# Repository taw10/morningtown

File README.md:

MorningTown: A silent alarm clock
=================================

Description
-----------

MorningTown is a silent alarm clock system based on a Raspberry Pi Pico.

At 7:15am, it lights a single green LED.  At 8am, it additionally lights a red
LED.  Around midday, it turns them both off.  Apart from an over-engineered
configuration system, it does literally nothing else.

Why???
------

You are supposed to get out of bed if you wake up and see the green light, or
perhaps doze until you see the red light as well.  If no lights are on, go
back to sleep.

Huh??
-----

[Awareness of the exact time is bad for your sleep](https://www.techradar.com/health-fitness/mattresses/clock-watching-could-be-killing-your-sleep-why-clocks-have-no-place-in-the-bedroom).

If you're having trouble getting to sleep, seeing the time will add stress
and make it even harder to sleep.  Similarly, knowing that your alarm will go off
shortly can prevent you from relaxing in the morning, and grabbing a valuable
few minutes' extra sleep.

MorningTown reduces information about the time down to a simple signal to say
either "Go back to sleep" or "Get up if you're ready".

In contrast to a clock radio or "artificial sunrise" lamp, there is no danger
of disturbing any other beings who share the room and may run on different
schedules.

I still have a number of questions
----------------------------------

Obviously, you should set an audible alarm clock for important wake-up calls.

Hardware
--------

The Pi Pico's real-time clock loses time when power is removed, so MorningTown
needs either a separate battery-backed RTC module, or to synchronise itself
using NTP on each startup.

### PCB with real-time clock and battery backup

Send the circuit board design in the `pcb` folder
([KiCad](https://www.kicad.org/) format) to your manufacturer of choice.
I have been using [Aisler](https://aisler.net/).

### Cheap and cheerful option

Solder red and green LEDs to GPIOs 22 and 21 respectively of a Raspberry Pi
Pico W, each with a 1.5 kOhm series resistor (you won't need much brightness).
There is a ground pad conveniently placed between these two pins.

You can use other GPIOs if you prefer - see below for configuration
instructions.

Firmware
--------

Edit `compile` to set the path to the [Pico SDK](https://github.com/raspberrypi/pico-sdk),
as well as your WLAN name and password if you are using a Pico W.

The changeover days for daylight savings are hard-coded for Europe (the last
Sundays of March and October).  Unfortunately, a full local time library is far
too big to fit on the Pico, so you will have to figure out the logic yourself
for other time zones.

Run `compile`, then copy `build/morningtown.uf2` to the Pico.

Operation
---------

Connect the Pico to any USB power supply.

When the (optional) test button is held, the LEDs indicate as follows:
* Red: NTP synchronised if applicable, otherwise always on.
* Green: RTC time OK (regardless of source).
* Board LED: WLAN connected if applicable, otherwise always on.

Licence
-------

MorningTown is based on a heavily modified version of one of the Pico SDK
examples (picow-ntp-client), copyright (c) 2022 Raspberry Pi (Trading) Ltd.,
under the BSD 3-clause licence.

MorningTown is free software: you can redistribute it and/or modify it under the
terms of the GNU General Public License as published by the Free Software
Foundation, either version 3 of the License, or (at your option) any later
version.

MorningTown is distributed in the hope that it will be useful, but WITHOUT ANY
WARRANTY; without even the implied warranty of MERCHANTABILITY or FITNESS FOR A
PARTICULAR PURPOSE.  See the GNU General Public License for more details.

You should have received a copy of the GNU General Public License along with
MorningTown.  If not, see <http://www.gnu.org/licenses/>.

About the name
--------------

It's like a railway signal for your sleep:

> Somewhere there is sunshine  
> Somewhere there is day  
> Somewhere there is Morning town  
> Many miles away

- [Malvina Reynolds](https://en.wikipedia.org/wiki/Morningtown_Ride)

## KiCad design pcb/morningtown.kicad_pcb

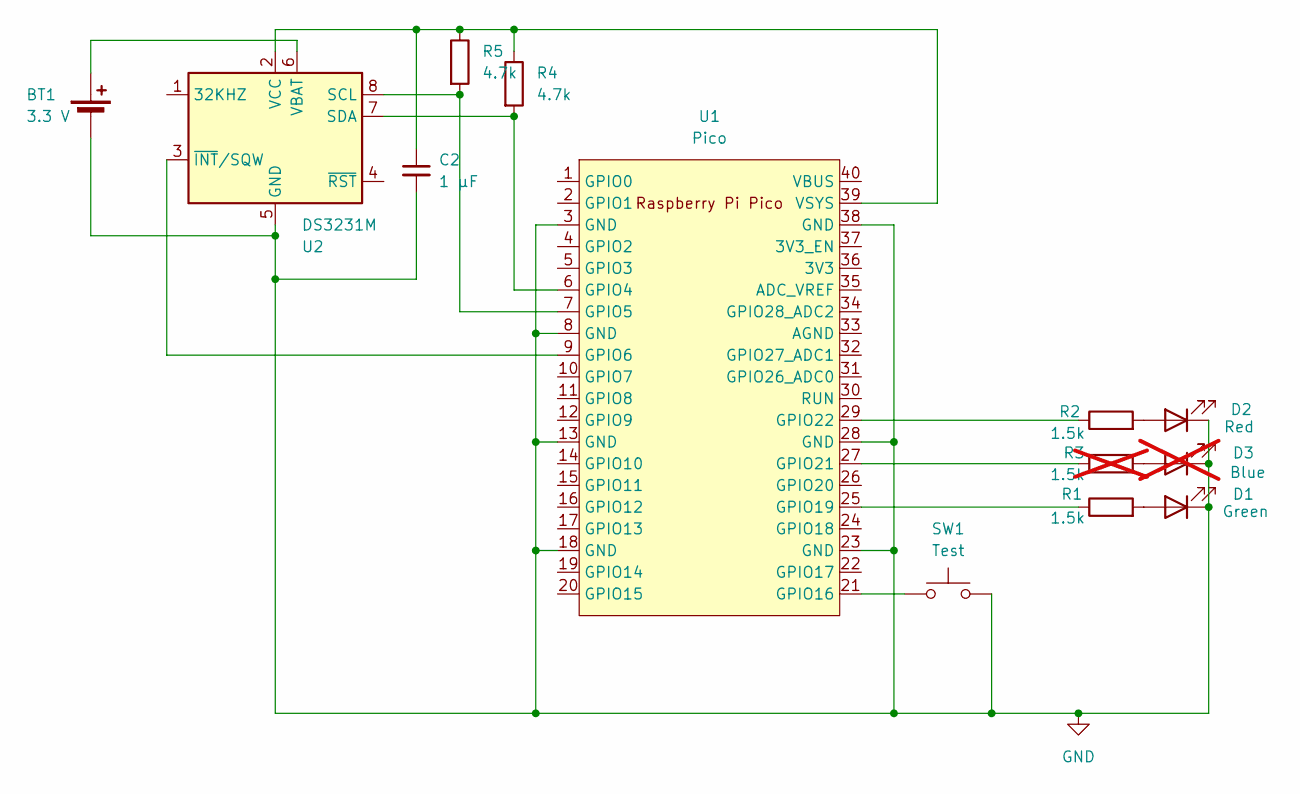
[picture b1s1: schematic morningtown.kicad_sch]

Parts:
BT1: 3.3 V; BatteryHolder_Keystone_3001_1x12mm
C2: 1 µF; C_0805_2012Metric_Pad1.18x1.45mm_HandSolder
D1: Green; LED_D5.0mm
D2: Red; LED_D5.0mm
D3: Blue; LED_D3.0mm; not fitted
R1, R2: 1.5k; R_0805_2012Metric_Pad1.20x1.40mm_HandSolder
R3: 1.5k; R_0805_2012Metric_Pad1.20x1.40mm_HandSolder; not fitted
R4, R5: 4.7k; R_0805_2012Metric_Pad1.20x1.40mm_HandSolder
SW1: Test; SW_PUSH_6mm
U1: Pico; RPi_Pico_W
U2: DS3231M; SOIC-8_3.9x4.9mm_P1.27mm

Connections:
GND: BT1.2 (-), C2.2, D1.1 (K), D2.1 (K), D3.1 (K), SW1.2, U1.3 (GND), U1.8 (GND), U1.13 (GND), U1.18 (GND), U1.23 (GND), U1.28 (GND), U1.38 (GND), U2.5 (GND)
unnamed: BT1.1 (+), U2.6 (VBAT)
unnamed: D1.2 (A), R1.2
unnamed: D2.2 (A), R2.2
unnamed: D3.2 (A), R3.2
unnamed: R4.2, U1.6 (GPIO4), U2.7 (SDA)
unnamed: R5.2, U1.7 (GPIO5), U2.8 (SCL)
unnamed: U1.9 (GPIO6), U2.3 (~INT/SQW)
unnamed: SW1.1, U1.21 (GPIO16)
unnamed: R1.1, U1.25 (GPIO19)
unnamed: R3.1, U1.27 (GPIO21)
unnamed: R2.1, U1.29 (GPIO22)
unnamed: C2.1, R4.1, R5.1, U1.39 (VSYS), U2.2 (VCC)

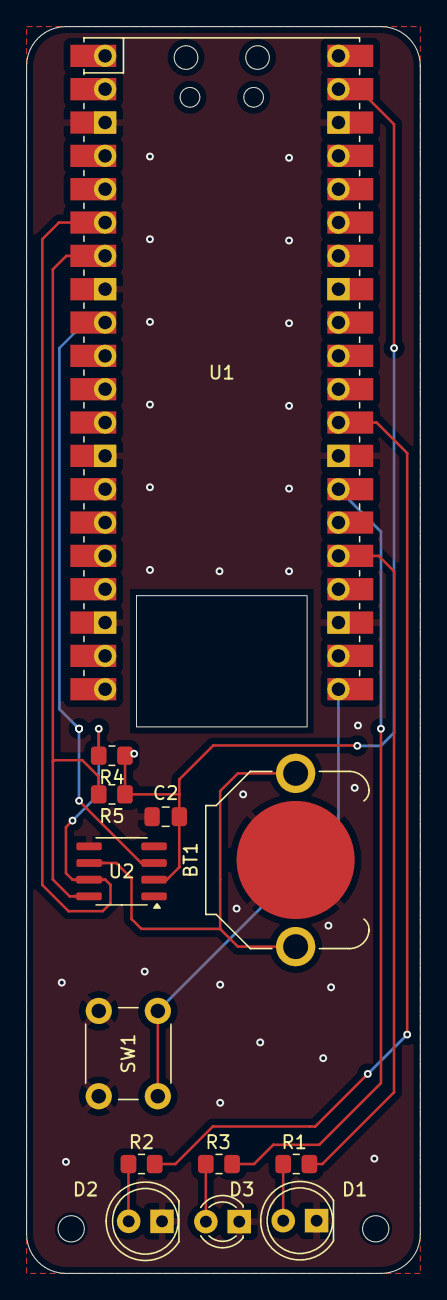
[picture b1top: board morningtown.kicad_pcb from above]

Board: 2 copper layers, 30.0 x 95.0 mm, 15 parts (0 on the bottom side), 13 nets.

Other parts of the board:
FrontL: MountingHole_2mm
FrontR: MountingHole_2mm

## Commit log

2023-02-05 Initial import
2023-02-16 Sleep while idle
2023-02-18 Synchronise using NTP
2023-02-19 Set host name
2023-02-19 Add README.md
2023-02-19 Add circuit diagram
2023-02-20 Move UTC offset to header
2023-02-22 Update README.md and add photo
2023-02-26 Add watchdog
2023-02-26 Add test button
2023-02-27 Test button should not have priority over clock LEDs
2023-03-02 Use pico_cyw43_arch_lwip_poll
    So little can be done in lwIP callbacks with the background driver, we
    end up polling anyway. So we might as well poll the driver directly,
    and be able to do more in the callbacks.
2023-03-03 Completely overhaul the code
    This gets rid of a lot of nasty callback stuff, and compartmentalises
    the NTP code much better.
2023-03-03 Re-request NTP time periodically
    Note that the terms of service for pool.ntp.org require that we not
    synchronise unreasonably often, and not at a regular time such as "top
    of the hour".
2023-03-03 Un-set ntp_ok if there's an error
2023-07-02 Slow down wifi associations, use LEDs less
    First, trying to re-connect to wifi every 10 seconds is way too fast.
    Second, if there's an error, keep quiet about it unless the button is
    pushed. The RTC will probably not drift too far...!
2023-09-17 compile: Add OpenOCD upload
2023-09-17 Add comments about mysterious constants
2024-10-27 Add basic DST handling
    ...and snarky comments.
2024-12-14 Change indentation style
2024-12-20 Fix lies in README.md
2024-12-20 Add demo DS3231 stuff
2024-12-20 Add parameters for nice PCB
2024-12-20 Enable compilation for non-W Pico
2024-12-20 Add PWM dimming for LEDs
2024-12-20 Update boot-up lightshow
2024-12-21 Move DS3231 to separate module, and expand it
2024-12-21 Add a basic serial terminal
    Has commands for setting clock etc.
2024-12-21 Get rid of unnecessary printf wrapper
2024-12-23 DS3231: Disable EN32KHZ bit on startup
    We don't use it. It's just wasting power.
2024-12-23 Add command to reset DS3231 Oscillator Stop Flag (OSF)
    This is used to detect if something bad happened to the clock.
2024-12-23 Report if Pico RTC doesn't seem to be running
2024-12-23 Ignore zero character
    This was preventing the first command from working.
2024-12-23 Note that internal clock time is always UTC
2024-12-23 Try to be more helpful on command line
2024-12-23 Require RTC to be running for green test light
2024-12-23 Add non-W board LED to startup lightshow
2024-12-24 Add Errata for 1.0
2024-12-29 Fix r1.0 errata
2025-01-01 Add ds3231_get_datetime
2025-01-01 Remove debug
2025-01-01 Factorise set_board_led
2025-01-01 Slow down clock checks to once every ten seconds
2025-01-01 Detect DS3231 at runtime
    Doing it at compile time doesn't give any benefit.
2025-01-01 Fix help message logic
2025-01-06 Show presence of DS3231 at startup
2025-01-06 ds3231_get_datetime: Add a return value
2025-01-07 Switch to SMD resistors and capacitors
2025-01-09 General tidy-up
2025-01-09 Use the DS3231 for time checking, if we have it
2025-01-09 If DS3231 works, then we know the time
    Not quite true: should check OSF
2025-01-09 Formatting
2025-03-03 Slow down I2C communication to DS3231
    The PCB lacks the pull-up resistors needed to go so fast.
2025-03-03 Fix DST calculation and lies in comments
2025-03-03 LED fixes
2025-03-03 Report if RTC set fails
2025-10-03 Fix DST calculation
2025-10-03 Fix help message
2025-12-27 Use polling instead of chars_available_callback
    When using USB serial, sending large amounts of text back over the port
    in the chars_available_callback causes bytes to be lost.
    This is kind of a cheap solution - calling getchar_timeout_us(0) in the
    main loop - but it works. When the USB serial port is connected, the
    loop executes faster to make it more responsive.
2026-03-15 Clarify days of the week
2026-03-15 Move firmware files into separate folder
2026-03-15 Move PCB files to separate folder
2026-03-15 Update compile script
2026-03-15 Move compile script to firmware directory
2026-03-15 Update KiCad files to latest version, update errata, add metadata
2026-03-15 Add .gitignore
2026-03-21 Low-level parts for persistent settings
2026-03-21 Set LED pin assignments via console/settings
2026-03-21 Fix error message
2026-03-22 Complain if DS3231 stop flag is set
2026-03-22 Set waking times and UTC offset via settings
2026-03-22 Set clear time via settings
2026-03-22 Fix clear/tz commands and help
2026-03-28 Work on PCB
2026-03-29 Add missing initialisation
    Fixes initial startup without any saved settings.
2026-04-09 Show local time settings
2026-04-09 Fix wonky integer types which broke everything
